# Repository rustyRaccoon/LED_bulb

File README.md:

# LED_bulb
 LED lightbulb to run on ~12V from e.g. 3 LiPos

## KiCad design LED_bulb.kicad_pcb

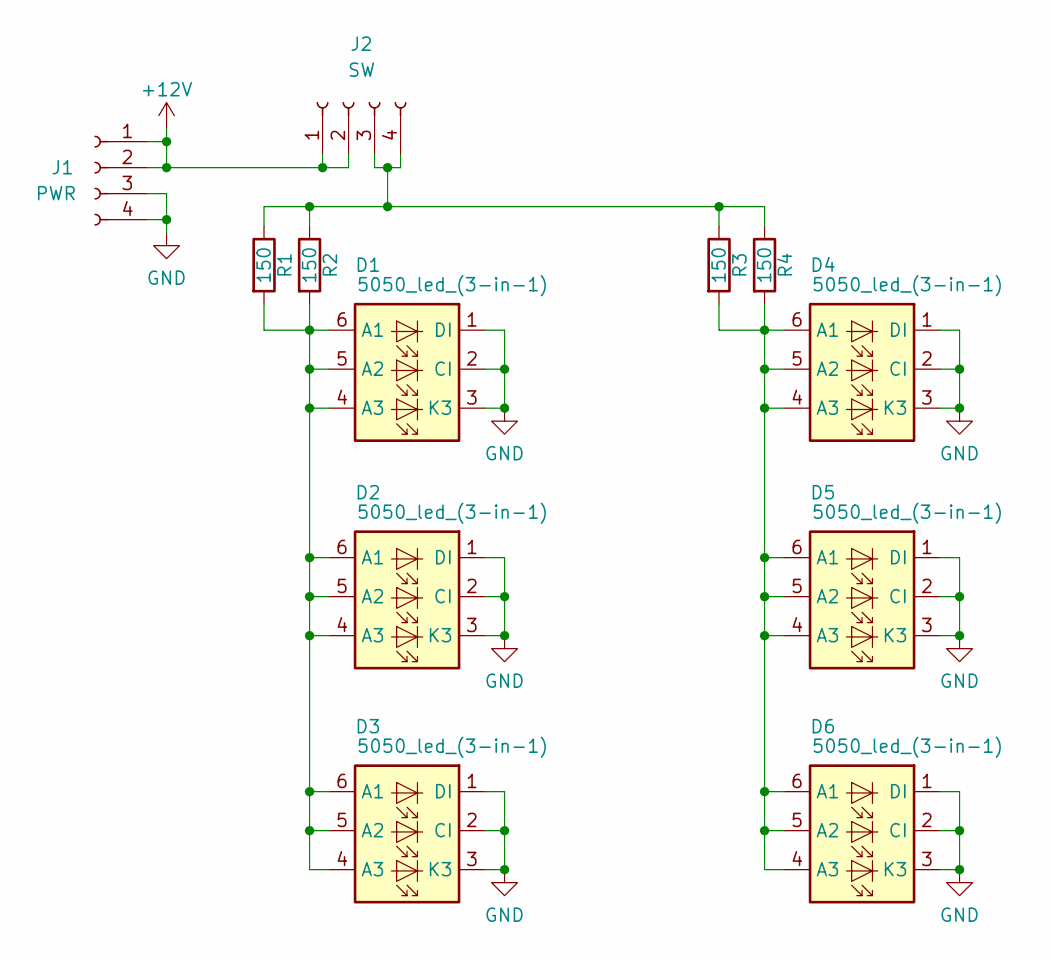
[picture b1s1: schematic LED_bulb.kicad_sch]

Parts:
D1, D2, D3, D4, D5, D6: 5050_led_(3-in-1); LED_RGB_5050-6
J1: PWR; PinHeader_1x04_P2.54mm_Vertical
J2: SW; PinHeader_1x04_P2.54mm_Vertical
R1, R2, R3, R4: 150; R_1206_3216Metric

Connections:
+12V: J1.1, J1.2, J2.1, J2.2
GND: D1.1 (DI), D1.2 (CI), D1.3 (K3), D2.1 (DI), D2.2 (CI), D2.3 (K3), D3.1 (DI), D3.2 (CI), D3.3 (K3), D4.1 (DI), D4.2 (CI), D4.3 (K3), D5.1 (DI), D5.2 (CI), D5.3 (K3), D6.1 (DI), D6.2 (CI), D6.3 (K3), J1.3, J1.4
unnamed: D1.4 (A3), D1.5 (A2), D1.6 (A1), D2.4 (A3), D2.5 (A2), D2.6 (A1), D3.4 (A3), D3.5 (A2), D3.6 (A1), R1.2, R2.2
unnamed: D4.4 (A3), D4.5 (A2), D4.6 (A1), D5.4 (A3), D5.5 (A2), D5.6 (A1), D6.4 (A3), D6.5 (A2), D6.6 (A1), R3.2, R4.2
unnamed: J2.3, J2.4, R1.1, R2.1, R3.1, R4.1

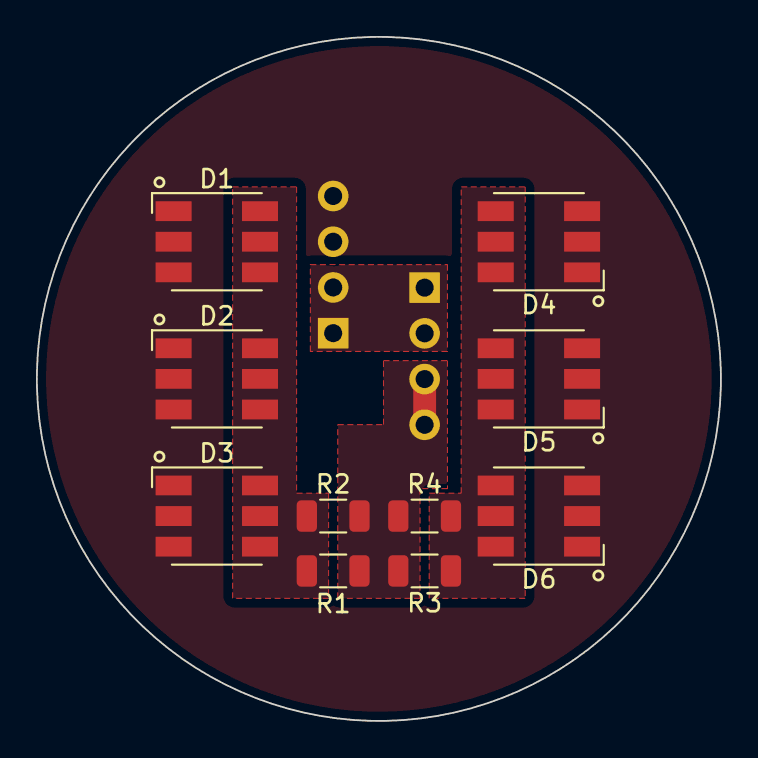
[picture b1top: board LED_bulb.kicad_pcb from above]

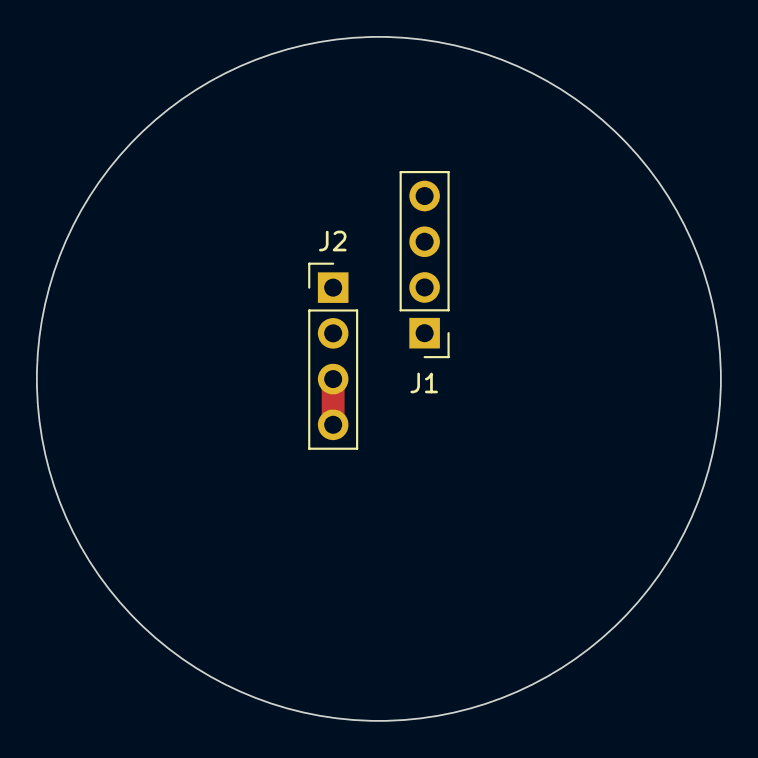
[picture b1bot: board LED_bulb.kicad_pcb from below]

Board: 2 copper layers, 38.0 x 38.0 mm, 12 parts (2 on the bottom side), 5 nets.
